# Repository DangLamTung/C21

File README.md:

# C21
 C21 microcontroller class of PIF CLB

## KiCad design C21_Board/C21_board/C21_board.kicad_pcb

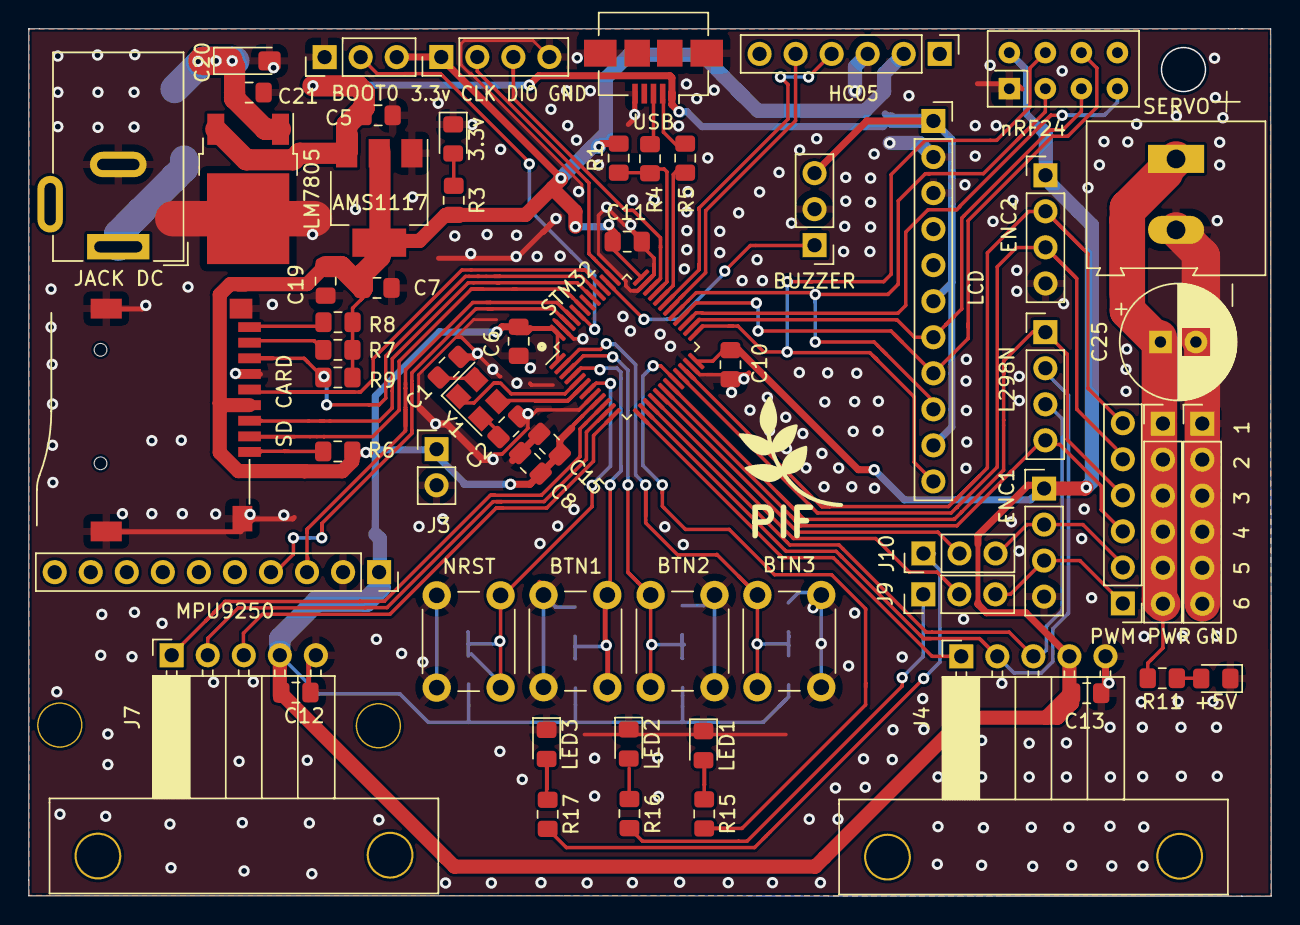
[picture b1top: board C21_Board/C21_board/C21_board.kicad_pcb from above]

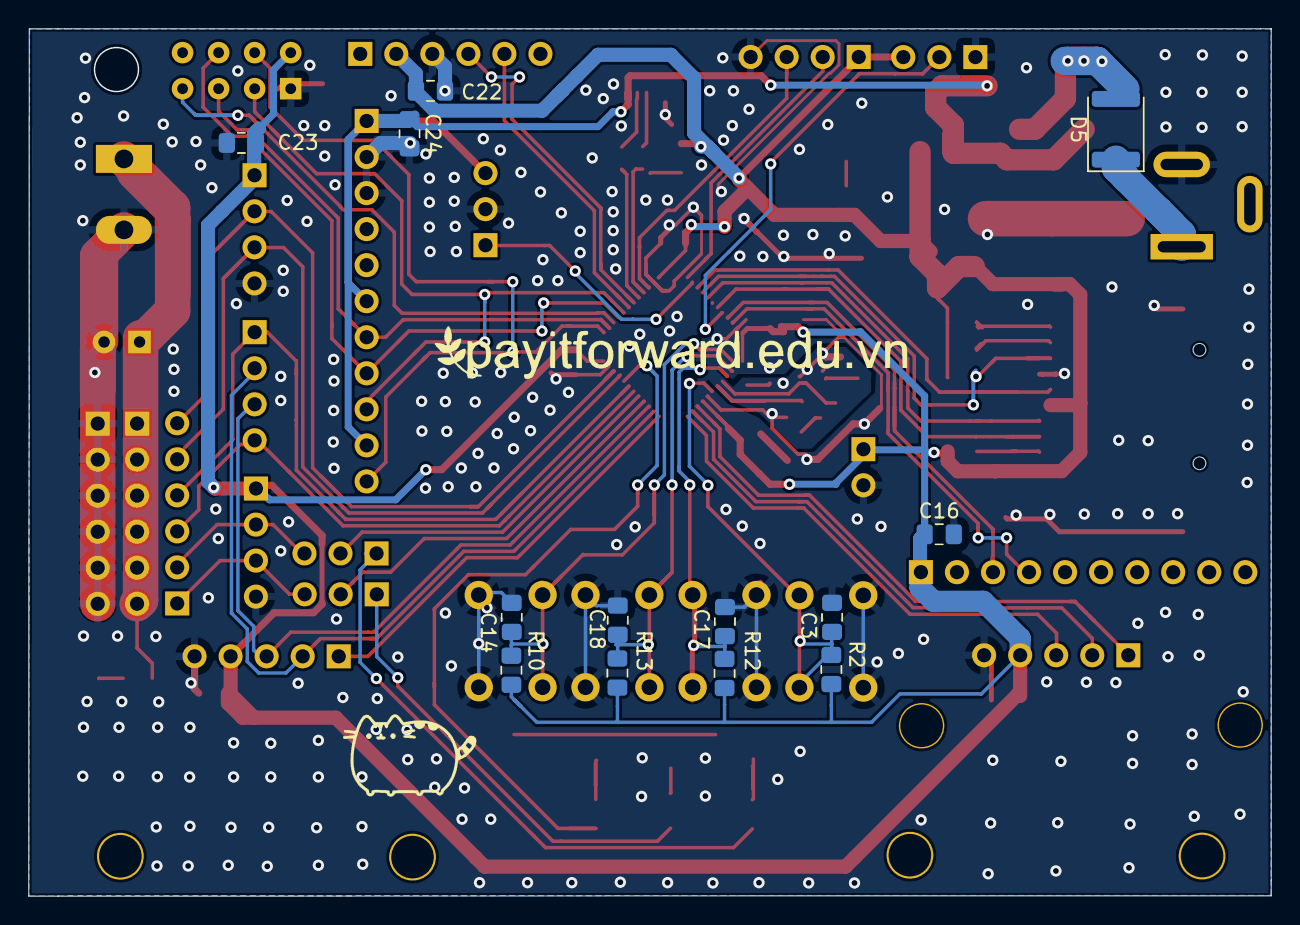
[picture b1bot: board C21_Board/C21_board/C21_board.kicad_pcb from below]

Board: 2 copper layers, 87.6 x 61.1 mm, 75 parts (13 on the bottom side), 60 nets.

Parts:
3.3v: LED; LED_0805_2012Metric_Pad1.15x1.40mm_HandSolder
3.3v CLK DIO GND: Debug; PinHeader_1x04_P2.54mm_Vertical
6  5  4  3  2  1: PWM; PinHeader_1x06_P2.54mm_Vertical
+5V: LED; LED_0805_2012Metric_Pad1.15x1.40mm_HandSolder
AMS1117: AMS1117-3.3; SOT-223-3_TabPin2
BOOT0: Boot; PinHeader_1x03_P2.54mm_Vertical
BTN1, BTN2, BTN3: SW_Push; SW_PUSH_6mm_H4.3mm
BUZZER: Buzzer; PinHeader_1x03_P2.54mm_Vertical
C1, C2: 18pF; C_0805_2012Metric_Pad1.15x1.40mm_HandSolder
C3, C5, C6, C7, C8, C10, C11, C12, C13, C14, C17, C18, C19, C21, C22, C23: 100n; C_0805_2012Metric_Pad1.15x1.40mm_HandSolder
C15: 1u; C_0805_2012Metric_Pad1.15x1.40mm_HandSolder
C16, C24: C; C_0805_2012Metric_Pad1.15x1.40mm_HandSolder
C20: 1uF; CP_EIA-3216-18_Kemet-A_Pad1.58x1.35mm_HandSolder
C25: 100uF; CP_Radial_D8.0mm_P2.50mm
D5: DIODE; D_1812_4532Metric
ENC1: Encoder 1; PinHeader_1x04_P2.54mm_Vertical
ENC2: Encoder 2; PinHeader_1x04_P2.54mm_Vertical
GND: GND; PinHeader_1x06_P2.54mm_Vertical
HC05: Conn_01x06_Male; PinHeader_1x06_P2.54mm_Vertical
J3: Conn_01x02_Male; PinHeader_1x02_P2.54mm_Vertical
J4: Joy 2; PinSocket_1x05_P2.54mm_Horizontal
J7: Joy 1; PinSocket_1x05_P2.54mm_Horizontal
J9: LED SW 1; PinHeader_1x03_P2.54mm_Vertical
J10: LED SW 2; PinHeader_1x03_P2.54mm_Vertical
JACK DC: Jack-DC; BarrelJack_Wuerth_6941xx301002
L298N: L298n Out; PinHeader_1x04_P2.54mm_Vertical
LCD: LCD; PinSocket_1x11_P2.54mm_Vertical
LED1, LED2, LED3: LED; LED_0805_2012Metric_Pad1.15x1.40mm_HandSolder
LM7805: L7805; TO-252-2
MPU9250: IMU; PinSocket_1x10_P2.54mm_Vertical
NRST: SW_Push; SW_PUSH_6mm_H4.3mm
PWM PWR: Power; PinHeader_1x06_P2.54mm_Vertical
R1: 1.5k; R_0805_2012Metric_Pad1.15x1.40mm_HandSolder
R2: R; R_0805_2012Metric_Pad1.15x1.40mm_HandSolder
R3, R11, R15, R16, R17: 330R; R_0805_2012Metric_Pad1.15x1.40mm_HandSolder
R4, R5: 22R; R_0805_2012Metric_Pad1.15x1.40mm_HandSolder
R6, R7, R8, R9, R10, R12, R13: 10k; R_0805_2012Metric_Pad1.15x1.40mm_HandSolder
SD CARD: ST-TF-003A; SUNTECH_ST-TF-003A
SERVO: Pwr In; TerminalBlock_Altech_AK300-2_P5.00mm
STM32: STM32F103C8Tx; LQFP-48_7x7mm_P0.5mm
USB: USB_B_Micro; USB_Micro-B_Amphenol_10104110_Horizontal
Y1: Crystal; Crystal_SMD_3225-4Pin_3.2x2.5mm
nRF24: NRF24L01_Breakout; nRF24L01_Breakout

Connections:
+3V3: 3.3v CLK DIO GND.1, AMS1117.2 (VO), BOOT0.3, C6.1, C7.1, C8.1, C10.1, C11.1, C12.1, C13.1, C15.1, C16.1, C19.1, C22.1, C23.1, ENC1.1, ENC2.1, HC05.2, J3.1, J4.4, J7.4, MPU9250.1, R1.2, R2.1, R3.2, R6.2, R7.2, R8.2, R9.2, R10.1, R12.1, R13.1, SD CARD.4 (VDD), STM32.1 (VBAT), STM32.9 (VDDA), STM32.24 (VDD), STM32.36 (VDD), STM32.48 (VDD), nRF24.2 (VCC)
+5V: AMS1117.3 (VI), BUZZER.3, C5.1, C24.1, LCD.1, LCD.6, LCD.10, LM7805.3 (OUT), USB.1 (VBUS)
+5VP: C25.1, PWM PWR.1, PWM PWR.2, PWM PWR.3, PWM PWR.4, PWM PWR.5, PWM PWR.6, R11.2, SERVO.1
+12V: D5.1 (K), JACK DC.1
BOOT0: BOOT0.2, STM32.44 (BOOT0)
Button1: BTN3.2, C14.1, R10.2, STM32.2 (PC13)
Button2: BTN2.2, C18.1, R13.2, STM32.3 (PC14)
Button3: BTN1.2, C17.1, R12.2, STM32.4 (PC15)
Buzzer: BUZZER.1, STM32.38 (PA15)
Encoder1A: 6 5 4 3 2 1.1, ENC1.3, J9.3
Encoder1B: 6 5 4 3 2 1.2, ENC1.2, J10.3
Encoder2A: 6 5 4 3 2 1.6, ENC2.2, STM32.22 (PB11)
Encoder2B: 6 5 4 3 2 1.5, ENC2.3, STM32.21 (PB10)
GND: 3.3v.1 (K), 3.3v CLK DIO GND.4, +5V.1 (K), AMS1117.1 (GND), BOOT0.1, BTN1.1, BTN2.1, BTN3.1, BUZZER.2, C1.2, C2.2, C3.2, C5.2, C6.2, C7.2, C8.2, C10.2, C11.2, C12.2, C13.2, C14.2, C15.2, C16.2, C17.2, C18.2, C19.2, C20.2, C21.2, C22.2, C23.2, C24.2, C25.2, ENC1.4, ENC2.4, GND.1, GND.2, GND.3, GND.4, GND.5, GND.6, HC05.3, J3.2, J4.5, J7.5, JACK DC.2, LCD.2, LCD.3, LED1.1 (K), LED2.1 (K), LED3.1 (K), LM7805.2 (GND), MPU9250.2, NRST.1, SD CARD.6 (VSS), SD CARD.G1 (GND), SD CARD.G2 (GND), SD CARD.G3 (GND), SD CARD.G4 (GND), SERVO.2, STM32.8 (VSSA), STM32.23 (VSS), STM32.35 (VSS), STM32.47 (VSS), USB.5 (GND), USB.6 (Shield), nRF24.1 (GND)
IMU_SCL: MPU9250.3, STM32.45 (PB8)
IMU_SDA: MPU9250.4, STM32.46 (PB9)
Joystick1_SW: J7.3, STM32.12 (PA2)
Joystick1_x: J7.1, STM32.10 (PA0)
Joystick1_y: J7.2, STM32.11 (PA1)
Joystick2_SW: J4.3, L298N.3, STM32.15 (PA5)
Joystick2_x: J4.1, STM32.13 (PA3)
Joystick2_y: J4.2, L298N.2, STM32.14 (PA4)
LCD_CS: LCD.11, STM32.25 (PB12), nRF24.4 (~CSN)
LCD_RS: LCD.9, STM32.29 (PA8), nRF24.3 (CE)
LED1: R15.2, STM32.20 (PB2)
LED2: J9.1, R16.2
LED3: J10.1, R17.2
MOSI: LCD.8, STM32.28 (PB15), nRF24.6 (MOSI)
NRST: C3.1, NRST.2, R2.2, STM32.7 (NRST)
unnamed: +5V.2 (A), R11.1
unnamed: C1.1, Y1.4
unnamed: C2.1, Y1.2
unnamed: C20.1, C21.1, D5.2 (A), LM7805.1 (IN)
unnamed: R5.2, USB.2 (D-)
unnamed: R4.2, USB.3 (D+)
unnamed: LED1.2 (A), R15.1
unnamed: LED2.2 (A), R16.1
unnamed: LED3.2 (A), R17.1
unnamed: R6.1, SD CARD.1 (DAT2)
unnamed: R7.1, SD CARD.8 (DAT1)
unnamed: R8.1, SD CARD.9 (CD)
unnamed: 3.3v.2 (A), R3.1
OSC1: STM32.5 (PD0), Y1.1
OSC2: STM32.6 (PD1), Y1.3
PA6: J9.2, STM32.16 (PA6)
PA7: J10.2, STM32.17 (PA7)
PWM1: 6 5 4 3 2 1.3, L298N.4, STM32.18 (PB0)
PWM2: 6 5 4 3 2 1.4, L298N.1, STM32.19 (PB1)
SCK: LCD.7, STM32.26 (PB13), nRF24.5 (SCK)
SD_CSN: SD CARD.2 (DAT3), STM32.43 (PB7)
SD_MISO: R9.1, SD CARD.7 (DAT0), STM32.40 (PB4)
SD_MOSI: SD CARD.3 (CMD), STM32.41 (PB5)
SD_SCK: SD CARD.5 (CLK), STM32.39 (PB3)
SWCLK: 3.3v CLK DIO GND.2, STM32.37 (PA14)
SWDIO: 3.3v CLK DIO GND.3, STM32.34 (PA13)
UART1_RX: HC05.4, STM32.31 (PA10)
UART1_TX: HC05.5, STM32.30 (PA9)
USB_D+: R1.1, R4.1, STM32.33 (PA12)
USB_D-: R5.1, STM32.32 (PA11)
nRF24_MISO: STM32.27 (PB14), nRF24.7 (MISO)

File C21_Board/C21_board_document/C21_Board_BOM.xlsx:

C21 board BOM list
Name | Value | Position | Size | Amount | Is needed for C21 Entrance? | Link + Image (From thegioiic, not needed to buy at thegioiic)
Capacitor SMD 100nF (Tụ điện dán 104 0805) | 104 (100nF) | C3, C5, C6, C7, C8, C10, C11, C12, C13, C14, C16, C17, C18, C19, C21,C22,C23, C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 | 0805 | 22 | Yes | https://www.thegioiic.com/products/tu-gom-0805-100pf-50v
Capacitor SMD 22pF (Tụ điện dán 22pF 0805) | 22pF | C1, C2 | 0805 | 2 | Yes | https://www.thegioiic.com/products/tu-gom-0805-22pf-50v
Capacitor THT 100uF (Tụ điện cắm, phân cực 100uF) | 100uF | C25 | 5mm | 1 | Yes | https://www.thegioiic.com/products/tu-hoa-100uf-16v-5x11mm-xuyen-lo
Capacitor SMD 1uF (Tụ điện dán 1uF 0805) | 1uF | C15 | 0805 | 1 |  | https://www.thegioiic.com/products/tu-gom-0805-1uf-16v
Capacitor SMD Tatalum 1uF (Tụ tatalum 2.2uF trở lên, 3216) | 1uF trở lên | C20 | 3216 | 1 |  | https://www.thegioiic.com/products/tu-tantalum-1uf-16v-1206-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
Button THT 4 Pin (Nút nhấn 4 chân cắm) |  | BTN1, BTN2, BTN3, NRST | 6*6mm | 4 | Yes | https://www.thegioiic.com/products/nut-nhan-6x6mm-cao-7mm-4-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
LED SMD 0805 (Led dán 0805, màu tự chọn) |  | LED1, LED2, LED3, 3.3v, +5v | 0805 | 5 | Yes (có thể bỏ led 5v) | https://www.thegioiic.com/products/led-xanh-la-0805-dan-smd-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
Resistor SMD 0805 (Trở dán 0805) 1.5kOhm | 1.5kOhm, (Trở dán 153, cỡ 0805) | R1 (Trở này cần chính xác chút) | 0805 | 1 | Yes | https://www.thegioiic.com/products/dien-tro-1-5-kohm-0805-5
Resistor SMD 0805 (Trở dán 0805) 22Ohm | 22Ohm, (Trở dán 220, cỡ 0805) | R4,R5 (Trở này là trở cho USB, cần chính xác chút :V ) | 0805 | 2 | Yes | https://www.thegioiic.com/products/dien-tro-22-ohm-0805-5
Resistor SMD 0805 (Trở dán 0805) 330Ohm | 330 Ohm (Trở dán 331, cỡ 0805) | R3,R11,R15,R16,R17 (Đây là trở hạn dòng cho led, cũng không cần quá chính xác) | 0805 | 5 | Yes | https://www.thegioiic.com/products/dien-tro-330-ohm-0805-1
Resistor SMD 0805 (Trở dán 0805) 10kOhm | 10 kOhm (Trở 103 dán, cỡ 0805) | R10,R13,R12,R2,R6,R8,R9 (Đây thường là trở kéo cao, không cần quá chính xác) | 0805 | 6 | Yes | https://www.thegioiic.com/products/dien-tro-10-5-kohm-0805-1
Linear Voltage Drop Regulator (LDO) AMS1117 | 3.3v | AMS1117 - 3.3V | SOT-223-3 | 1 | Yes | http://www.tme.vn/Product.aspx?id=437#page=pro_info
Linear Voltage Drop Regulator (LDO) LM7805 | 5v | U4 | TO 252 | 1 | Yes | https://banlinhkien.com/78m05-to252-p6651257.html
USB micro SMD (Cổng microUSB dán) |  | USB | Micro USB SMD | 1 | Yes | https://www.thegioiic.com/products/cong-usb-micro-b-2-0-dau-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
Jack DC |  | Jack DC | Jack DC 2.5mm | 1 | Yes | https://www.thegioiic.com/products/dc5525-dau-noi-nguon-dc-c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
Micro SD card | Đầu gắn thẻ nhớ SD | MicroSD | MicroSD | 1 |  | https://www.thegioiic.com/products/misd-pp-9p-v2-khay-the-nh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
STM32F103C8T6 ( Vi điều khiển STM32F103C8T6) | STM32F103C8T6 | STM32F103C8T6 IC, 48 chân | LQFP48 | 1 | Yes | https://www.thegioiic.com/products/stm32f103c8t6
Crystal 8Mhz 3225 (Thạch anh 4 chân dán 3225) | 8MHz | Y1 |  | 1 |  | https://www.thegioiic.com/products/thach-anh-8mhz-3225-4-chan-smd
Domino 5mm 2 Pin | 5mm | Servo (Cổng nguồn cho Servo, Optional) | 5mm | 1 |  | Hàng rào sẽ được bán theo cây và các bạn có thể bẻ theo ý thích nên mình chỉ đư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
Header 3 Pin Male (Hàng rào đực 2.54mm) |  | Buzzer (Optional) , BOOT (Chọn mode Boot, Optional) , J9, J10 (Chọn mode LED, b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 | 2.54*3mm | 4 | Yes (Hàn J9, J10) | https://www.thegioiic.com/products/hang-rao-cai-don-2-54mm-1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
Header 4 Pin Male (Hàng rào đực 2.54mm) |  | 3.3v CLK DIO GND (cổng nạp), L298N, ENC1, ENC2 (Các cổng động cơ) | 2.54*4mm | 4 |  | https://www.thegioiic.com/products/hang-rao-cai-don-2-54mm-1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
Header 5 Pin Female (Hàng rào cái 2.54mm) |  | J4, J7 (Đây là 2 cổng cắm Joystick, có đổi thành header đực nếu không muốn dùng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 | 2.54*5mm | 5
Header 6 Pin Female (Hàng rào cái 2.54mm) |  | HC05 (Cổng ra cho HC05, có thể thay thành hàng rào đực nếu thích) | 2.54*6mm | 1
Header 6 Pin Male (Hàng rào đực 2.54mm) |  | PWM, PWR, GND (Cổng ra cho động cơ Servo, có thể dùng để chạy tay máy hoặc ESC,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 | 2.54*6mm | 3
Header 10 Pin Female (Hàng rào cái 2.54mm) |  | MPU9250 (Đây là cổng ra cho MPU9250/MPU6050, Optional) | 2.54*10mm | 1
Header 11 Pin Female (Hàng rào cái 2.54mm) |  | LCD (Cổng ra để gắn màn hình LCD TFT ST7735, Optional) | 2.54*11mm | 1
Header 4 Pin Female *2 (Hàng rào cái đôi 2.54mm) |  | nRF24 (Cổng ra cho NRF24, Optional) | 2.54*4*2 mm | 1
Diode SMD (Diode dán) |  | D2 (Diode chống ngược, có thể chọn loại diode chỉnh lưu bình thường) | 4532(Có thể chọn cỡ nhỏ hơn) | 1 | Yes | https://www.thegioiic.com/products/rs1m-sma-diode-chinh-luu-1a-1kv
Các trang mua hàng: thegioiic.com, caka.vn, tme.vn, banlinhkien.com, nshop.com,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
Lưu ý: + Các bạn cần hàn hết những linh kiện được đánh dấu cần thiết cho C21 để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
+ Nếu hàn hết thì cũng không cộng điểm nhé :V
+ Tiêu chí chấm điểm: 1. Hàn chạy: 10pt, Tức con chip STM32 nạp được code, chạy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
2. Hàn đẹp: Thế nào là hàn đẹp: 10pt, Không bị những lỗi sau:https://www.seeeds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
3. Khen giám khảo đẹp trai : 100pt :))))))))))

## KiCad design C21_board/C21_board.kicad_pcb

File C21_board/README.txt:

Creator: {Flu true} {Sneez true}

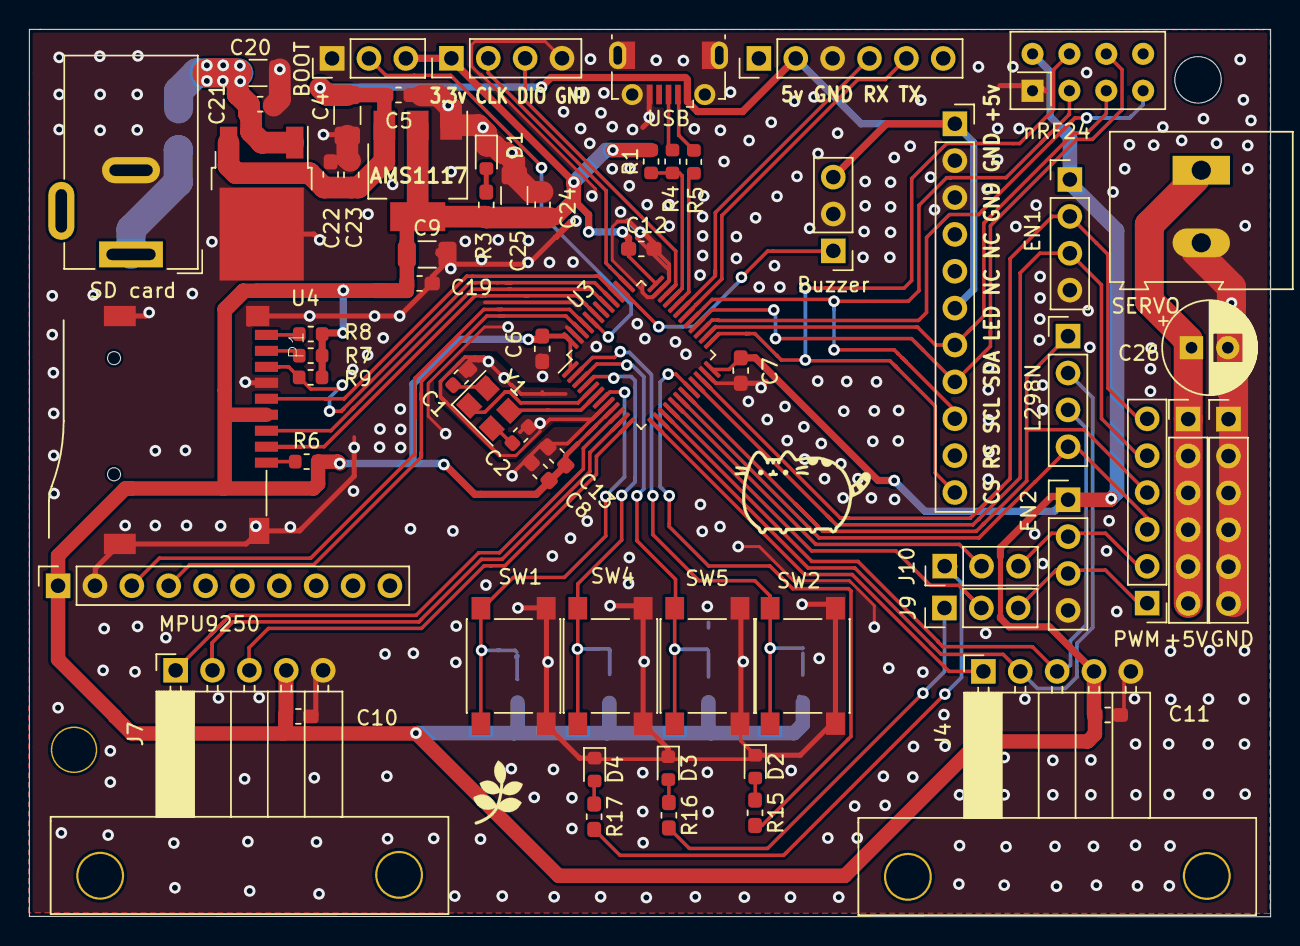
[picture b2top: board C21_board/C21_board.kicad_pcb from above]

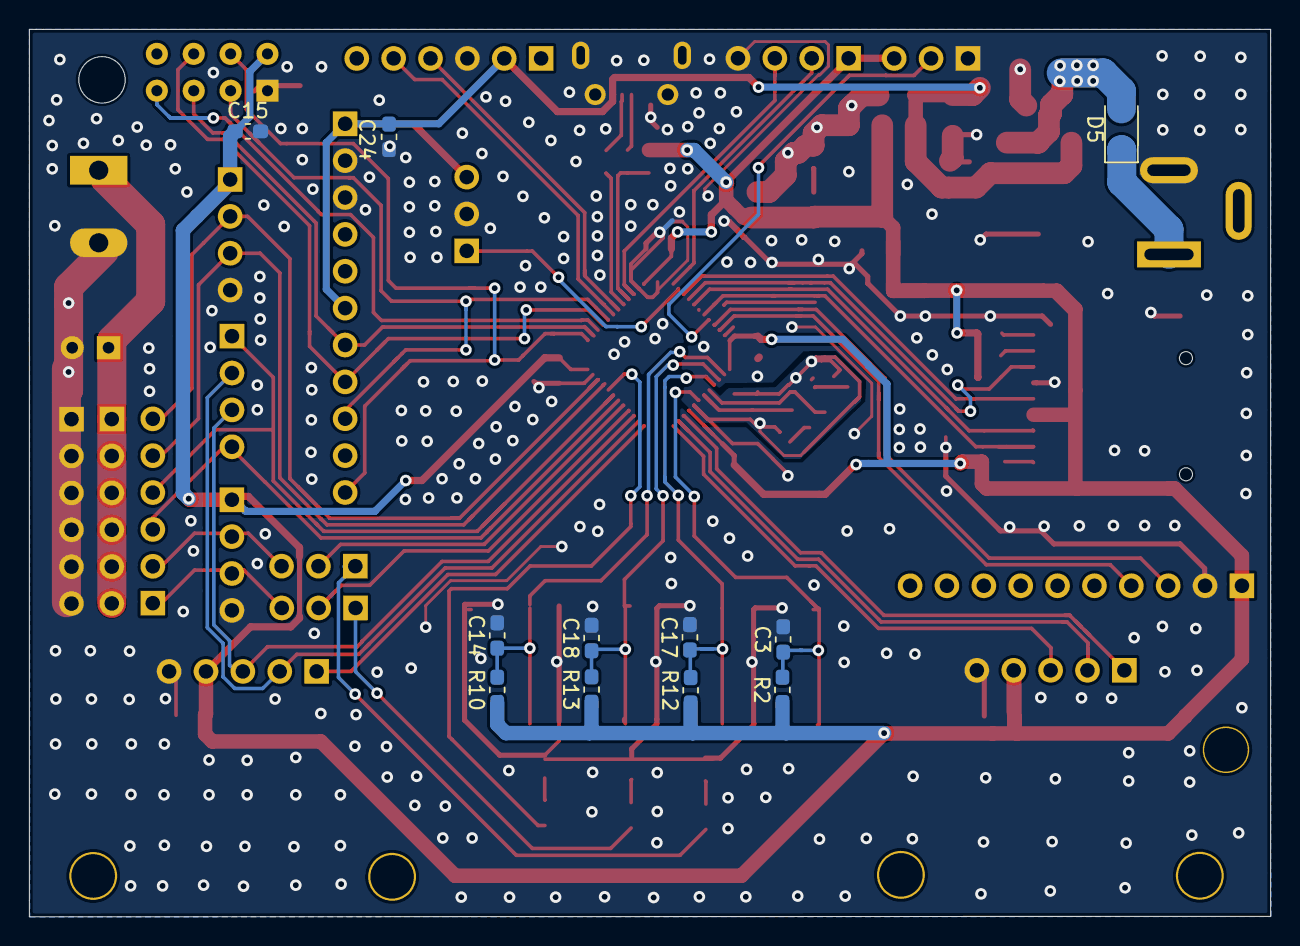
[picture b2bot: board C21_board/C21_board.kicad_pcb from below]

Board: 2 copper layers, 85.5 x 61.1 mm, 75 parts (11 on the bottom side), 59 nets.

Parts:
3.3v CLK DIO GND: Debug; PinHeader_1x04_P2.54mm_Vertical
5v GND RX TX: Conn_01x06_Male; PinHeader_1x06_P2.54mm_Vertical
+5V: Power; PinHeader_1x06_P2.54mm_Vertical
AMS1117: AMS1117-3.3; SOT-223-3_TabPin2
BOOT: Boot; PinHeader_1x03_P2.54mm_Vertical
Buzzer: Buzzer; PinHeader_1x03_P2.54mm_Vertical
C1, C2: 18pF; C_0603_1608Metric
C3, C5, C7, C12, C13, C14, C17, C18, C19, C24, C24#2: C; C_0603_1608Metric_Pad1.05x0.95mm_HandSolder
C4, C9, C20, C25: CP; C_1206_3216Metric
C6, C8, C10, C11, C21, C22, C23: 100n; C_0603_1608Metric_Pad1.05x0.95mm_HandSolder
C15: 1u; C_0603_1608Metric_Pad1.05x0.95mm_HandSolder
C26: CP; CP_Radial_D6.3mm_P2.50mm
CS RS SCL SDA LED NC NC GND GND +5v     : LCD; PinSocket_1x11_P2.54mm_Vertical
D1, D2, D3, D4: LED; LED_0603_1608Metric
D5: DIODE; D_1206_3216Metric
EN1: Encoder 2; PinHeader_1x04_P2.54mm_Vertical
EN2: Encoder 1; PinHeader_1x04_P2.54mm_Vertical
GND: GND; PinHeader_1x06_P2.54mm_Vertical
J4: Joy 2; PinSocket_1x05_P2.54mm_Horizontal
J7: Joy 1; PinSocket_1x05_P2.54mm_Horizontal
J9: LED SW 1; PinHeader_1x03_P2.54mm_Vertical
J10: LED SW 2; PinHeader_1x03_P2.54mm_Vertical
L298N: L298n Out; PinHeader_1x04_P2.54mm_Vertical
MPU9250: IMU; PinSocket_1x10_P2.54mm_Vertical
P1: ST-TF-003A; SUNTECH_ST-TF-003A
PWM: PWM; PinHeader_1x06_P2.54mm_Vertical
R1: 1.5k; R_0603_1608Metric
R2, R3, R10, R12, R13, R15, R16, R17: R; R_0603_1608Metric_Pad1.05x0.95mm_HandSolder
R4, R5: 22R; R_0603_1608Metric
R6, R7, R8, R9: 10k; R_0603_1608Metric
SD card: Jack-DC; BarrelJack_Wuerth_6941xx301002
SERVO : Pwr In; TerminalBlock_Altech_AK300-2_P5.00mm
SW1, SW2, SW4, SW5: SW_Push; SW_Push_1P1T_NO_6x6mm_H9.5mm
U3: STM32F103C8Tx; LQFP-48_7x7mm_P0.5mm
U4: L7805; TO-252-2
USB: USB_B_Micro; USB_Micro-B_Molex-105017-0001
Y1: Crystal; Crystal_SMD_3225-4Pin_3.2x2.5mm
nRF24: NRF24L01_Breakout; nRF24L01_Breakout

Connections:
+3V3: 3.3v CLK DIO GND.1, AMS1117.2, BOOT.3, C6.1, C7.1, C8.1, C9.1, C10.1, C11.1, C12.1, C13.1, C15.1, C19.1, C24.1, C25.1, EN1.1, EN2.1, J4.4, J7.4, MPU9250.1, P1.4, R1.2, R2.1, R3.2, R6.2, R7.2, R8.2, R9.2, R10.1, R12.1, R13.1, U3.1, U3.9, U3.24, U3.36, U3.48, nRF24.2
+5V: 5v GND RX TX.2, AMS1117.3, Buzzer.3, C4.1, C5.1, C22.1, C23.1, C24#2.1, CS RS SCL SDA LED NC NC GND GND +5v.1, CS RS SCL SDA LED NC NC GND GND +5v.6, U4.3, USB.1
+5VP: +5V.1, +5V.2, +5V.3, +5V.4, +5V.5, +5V.6, C26.1, SERVO.1
+12V: D5.1, SD card.1
BOOT0: BOOT.2, U3.44
Button1: C14.1, R10.2, SW2.2, U3.2
Button2: C18.1, R13.2, SW5.2, U3.3
Button3: C17.1, R12.2, SW4.2, U3.4
Buzzer: Buzzer.1, U3.38
Encoder1A: EN2.3, J9.3, PWM.1
Encoder1B: EN2.2, J10.3, PWM.2
Encoder2A: EN1.2, PWM.6, U3.22
Encoder2B: EN1.3, PWM.5, U3.21
GND: 3.3v CLK DIO GND.4, 5v GND RX TX.3, AMS1117.1, BOOT.1, Buzzer.2, C1.2, C2.2, C3.2, C4.2, C5.2, C6.2, C7.2, C8.2, C9.2, C10.2, C11.2, C12.2, C13.2, C14.2, C15.2, C17.2, C18.2, C19.2, C20.2, C21.2, C22.2, C23.2, C24.2, C24#2.2, C25.2, C26.2, CS RS SCL SDA LED NC NC GND GND +5v.2, CS RS SCL SDA LED NC NC GND GND +5v.3, D1.1, D2.1, D3.1, D4.1, EN1.4, EN2.4, GND.1, GND.2, GND.3, GND.4, GND.5, GND.6, J4.5, J7.5, MPU9250.2, P1.6, P1.G1, P1.G2, P1.G3, P1.G4, SD card.2, SERVO.2, SW1.1, SW2.1, SW4.1, SW5.1, U3.8, U3.23, U3.35, U3.47, U4.2, USB.5, USB.6, nRF24.1
IMU_SCL: MPU9250.3, U3.45
IMU_SDA: MPU9250.4, U3.46
Joystick1_SW: J7.3, U3.12
Joystick1_x: J7.1, U3.10
Joystick1_y: J7.2, U3.11
Joystick2_SW: J4.3, L298N.3, U3.15
Joystick2_x: J4.1, U3.13
Joystick2_y: J4.2, L298N.2, U3.14
LCD_CS: CS RS SCL SDA LED NC NC GND GND +5v.11, U3.25, nRF24.4
LCD_RS: CS RS SCL SDA LED NC NC GND GND +5v.9, U3.29, nRF24.3
LED1: R15.2, U3.20
LED2: J9.1, R16.2
LED3: J10.1, R17.2
MOSI: CS RS SCL SDA LED NC NC GND GND +5v.8, U3.28, nRF24.6
NRST: C3.1, R2.2, SW1.2, U3.7
unnamed: C1.1, Y1.4
unnamed: C2.1, Y1.2
unnamed: C20.1, C21.1, D5.2, U4.1
unnamed: D1.2, R3.1
unnamed: D2.2, R15.1
unnamed: D3.2, R16.1
unnamed: D4.2, R17.1
unnamed: R5.2, USB.2
unnamed: R4.2, USB.3
unnamed: P1.1, R6.1
unnamed: P1.8, R7.1
unnamed: P1.9, R8.1
OSC1: U3.5, Y1.1
OSC2: U3.6, Y1.3
PA6: J9.2, U3.16
PA7: J10.2, U3.17
PWM1: L298N.4, PWM.3, U3.18
PWM2: L298N.1, PWM.4, U3.19
SCK: CS RS SCL SDA LED NC NC GND GND +5v.7, U3.26, nRF24.5
SD_CSN: P1.2, U3.43
SD_MISO: P1.7, R9.1, U3.40
SD_MOSI: P1.3, U3.41
SD_SCK: P1.5, U3.39
SWCLK: 3.3v CLK DIO GND.2, U3.37
SWDIO: 3.3v CLK DIO GND.3, U3.34
UART1_RX: 5v GND RX TX.4, U3.31
UART1_TX: 5v GND RX TX.5, U3.30
USB_D+: R1.1, R4.1, U3.33
USB_D-: R5.1, U3.32
nRF24_MISO: U3.27, nRF24.7

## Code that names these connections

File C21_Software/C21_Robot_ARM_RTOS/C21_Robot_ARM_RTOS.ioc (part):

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Mcu.Name=STM32F103C(8-B)Tx
Mcu.Package=LQFP48
Mcu.UserName=STM32F103C8Tx
PA1.Signal=ADCx_IN1
PA10.Mode=Asynchronous
PA10.Signal=USART1_RX
PA11.Mode=Device
PA11.Signal=USB_DM
PA12.Mode=Device
PA12.Signal=USB_DP
PA13.Mode=Serial_Wire
PA13.Signal=SYS_JTMS-SWDIO
PA14.Mode=Serial_Wire
PA14.Signal=SYS_JTCK-SWCLK
PA2.Signal=ADCx_IN2
PA4.Signal=ADCx_IN4
PA5.Signal=ADCx_IN5
PA6.Signal=S_TIM3_CH1
PA7.Signal=S_TIM3_CH2
PA8.Signal=GPIO_Output
PA9.Mode=Asynchronous
PA9.Signal=USART1_TX
PB0.Signal=S_TIM3_CH3
PB1.Signal=S_TIM3_CH4
PB10.Signal=S_TIM2_CH3
PB11.Signal=S_TIM2_CH4
PB12.Signal=GPIO_Output
PB13.Mode=Full_Duplex_Master
PB13.Signal=SPI2_SCK
PB14.Mode=Full_Duplex_Master
PB14.Signal=SPI2_MISO
PB15.Mode=Full_Duplex_Master
PB15.Signal=SPI2_MOSI
PB3.Mode=Full_Duplex_Master
PB3.Signal=SPI1_SCK
PB4.Mode=Full_Duplex_Master
PB4.Signal=SPI1_MISO
PB5.Mode=Full_Duplex_Master
PB5.Signal=SPI1_MOSI
PB7.Signal=GPIO_Output
PC13-TAMPER-RTC.Signal=GPXTI13
PC14-OSC32_IN.Signal=GPXTI14
PC15-OSC32_OUT.Signal=GPXTI15
PD0-OSC_IN.Mode=HSE-External-Oscillator
PD0-OSC_IN.Signal=RCC_OSC_IN
PD1-OSC_OUT.Mode=HSE-External-Oscillator
PD1-OSC_OUT.Signal=RCC_OSC_OUT
RCC.SYSCLKFreq_VALUE=72000000
RCC.SYSCLKSource=RCC_SYSCLKSOURCE_PLLCLK
board=custom

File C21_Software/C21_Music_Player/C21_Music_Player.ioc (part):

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Mcu.Name=STM32F103C(8-B)Tx
Mcu.Package=LQFP48
Mcu.UserName=STM32F103C8Tx
PA10.Signal=GPIO_Output
PA11.Mode=Device
PA11.Signal=USB_DM
PA12.Mode=Device
PA12.Signal=USB_DP
PA13.Mode=Serial_Wire
PA13.Signal=SYS_JTMS-SWDIO
PA14.Mode=Serial_Wire
PA14.Signal=SYS_JTCK-SWCLK
PA15.Signal=S_TIM2_CH1_ETR
PA2.Mode=Asynchronous
PA2.Signal=USART2_TX
PA3.Mode=Asynchronous
PA3.Signal=USART2_RX
PA6.Signal=GPIO_Output
PA7.Signal=GPIO_Output
PA8.Signal=GPIO_Output
PA9.Signal=GPIO_Output
PB1.Signal=GPIO_Output
PB10.Signal=GPIO_Output
PB11.Signal=S_TIM2_CH4
PB13.Mode=Full_Duplex_Master
PB13.Signal=SPI2_SCK
PB14.Mode=Full_Duplex_Master
PB14.Signal=SPI2_MISO
PB15.Mode=Full_Duplex_Master
PB15.Signal=SPI2_MOSI
PB2.Signal=GPIO_Output
PB3.Mode=Full_Duplex_Master
PB3.Signal=SPI1_SCK
PB4.Mode=Full_Duplex_Master
PB4.Signal=SPI1_MISO
PB5.Mode=Full_Duplex_Master
PB5.Signal=SPI1_MOSI
PB7.GPIOParameters=GPIO_Label
PB7.GPIO_Label=SD_CS
PB7.Signal=GPIO_Output
PC13-TAMPER-RTC.Signal=GPXTI13
PC14-OSC32_IN.Signal=GPXTI14
PC15-OSC32_OUT.Signal=GPXTI15
PD0-OSC_IN.Mode=HSE-External-Oscillator
PD0-OSC_IN.Signal=RCC_OSC_IN
PD1-OSC_OUT.Mode=HSE-External-Oscillator
PD1-OSC_OUT.Signal=RCC_OSC_OUT
RCC.SYSCLKFreq_VALUE=72000000
RCC.SYSCLKSource=RCC_SYSCLKSOURCE_PLLCLK
board=custom

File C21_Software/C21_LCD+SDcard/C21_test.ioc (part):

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Mcu.Name=STM32F103C(8-B)Tx
Mcu.Package=LQFP48
Mcu.UserName=STM32F103C8Tx
PA13.Mode=Serial_Wire
PA13.Signal=SYS_JTMS-SWDIO
PA14.Mode=Serial_Wire
PA14.Signal=SYS_JTCK-SWCLK
PA6.Signal=GPIO_Output
PA7.Signal=GPIO_Output
PA8.GPIOParameters=GPIO_Label
PA8.GPIO_Label=LCD_RS
PA8.Signal=GPIO_Output
PA9.GPIOParameters=GPIO_Label
PA9.GPIO_Label=rst
PA9.Signal=GPIO_Output
PB12.GPIOParameters=GPIO_Label
PB12.GPIO_Label=LCD_CS
PB12.Signal=GPIO_Output
PB13.Mode=Full_Duplex_Master
PB13.Signal=SPI2_SCK
PB14.Mode=Full_Duplex_Master
PB14.Signal=SPI2_MISO
PB15.Mode=Full_Duplex_Master
PB15.Signal=SPI2_MOSI
PB2.Signal=GPIO_Output
PB3.Mode=Full_Duplex_Master
PB3.Signal=SPI1_SCK
PB4.Mode=Full_Duplex_Master
PB4.Signal=SPI1_MISO
PB5.Mode=Full_Duplex_Master
PB5.Signal=SPI1_MOSI
PB7.GPIOParameters=GPIO_Label
PB7.GPIO_Label=SD_CS
PB7.Signal=GPIO_Output
PD0-OSC_IN.Mode=HSE-External-Oscillator
PD0-OSC_IN.Signal=RCC_OSC_IN
PD1-OSC_OUT.Mode=HSE-External-Oscillator
PD1-OSC_OUT.Signal=RCC_OSC_OUT
RCC.SYSCLKFreq_VALUE=72000000
RCC.SYSCLKSource=RCC_SYSCLKSOURCE_PLLCLK
board=custom

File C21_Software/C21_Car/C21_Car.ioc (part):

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Mcu.Name=STM32F103C(8-B)Tx
Mcu.Package=LQFP48
Mcu.UserName=STM32F103C8Tx
PA0-WKUP.Signal=S_TIM2_CH1_ETR
PA1.Signal=S_TIM2_CH2
PA10.Mode=Asynchronous
PA10.Signal=USART1_RX
PA13.Mode=Serial_Wire
PA13.Signal=SYS_JTMS-SWDIO
PA14.Mode=Serial_Wire
PA14.Signal=SYS_JTCK-SWCLK
PA4.Signal=GPIO_Output
PA5.Signal=GPIO_Output
PA9.Mode=Asynchronous
PA9.Signal=USART1_TX
PB0.Signal=S_TIM3_CH3
PB1.Signal=S_TIM3_CH4
PB10.Signal=S_TIM2_CH3
PB11.Signal=S_TIM2_CH4
PB2.GPIOParameters=GPIO_Label
PB2.GPIO_Label=LED
PB2.Signal=GPIO_Output
PB8.Mode=I2C
PB8.Signal=I2C1_SCL
PB9.Mode=I2C
PB9.Signal=I2C1_SDA
PC13-TAMPER-RTC.GPIOParameters=GPIO_PuPd
PC13-TAMPER-RTC.GPIO_PuPd=GPIO_PULLUP
PC13-TAMPER-RTC.Signal=GPXTI13
RCC.SYSCLKFreq_VALUE=64000000
RCC.SYSCLKSource=RCC_SYSCLKSOURCE_PLLCLK
board=custom

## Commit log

2020-09-18 add hardware
2020-09-18 add 3d model
2020-09-19 add PWM code
2020-09-25 add music player
2020-09-25 update wav player code
2020-09-25 flappybird
2020-09-26 add robot arm
2020-09-28 add image
2020-09-28 add robot arm rtos
2020-09-28 add stepper extension
2020-09-29 add alot of thing
2020-09-29 flappybird complete
2020-09-30 remove fatfs
2020-10-01 add 3d box
2020-10-02 add 3d file
2020-10-02 add 3d for xe can bang
2020-10-02 add dxf file
2020-10-07 C21 car
2020-10-07 add car controller
2020-10-09 change code
2020-10-12 add quiz website
2020-10-12 add web
2020-10-12 add C21 web
2020-10-14 add last thing to do
2020-10-19 add final version of C21 board
2020-10-19 add BOM
2020-10-23 update slide for the second day
2020-10-23 add answer for the first exercise
2020-10-23 add logic level
2020-10-24 fix fake board
2020-11-04 fix BOM error
2020-11-09 fix BOM
